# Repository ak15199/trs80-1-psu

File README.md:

# TRS-80 Model 1 Power Supply and Case

A lot of great work has been done by Dan Bear and others over the years to recreate the now virtually impossible to acquire power supply for the TRS-80 Model 1. 

Researching prior art, I set out to create something that - although larger than the original - would not look out of place.

This repository contains the schematic and PCB layout along with the separate models required to 3D print the case. There's also a model to cover the exposed contacts on the fuse caddy.

Once built, you'll need to set the solder jumpers accordingly. There are two links to close if you're running on 110V, and one for 220V. Be careful to ensure that only the correctly labeled jumbers are closed.

Note that I have only built and tested the 110V version, so caution should be taken to test if you're building this to run on 220V.

If you would to use a different case and install an external fuse caddy, then there's a jumper for that too.

The lid of the case is designed to accept four 5.5 dia x 6mm long M4 threaded inserts. I used four M4 x 8mm pan head machine screws to retain the base.

Merge the TRS and Lid STLs if you have a dual extruder system, or don't load the TRS file if you prefer a recessed look. The lid will need to be rotated 180 degrees to avoid supports.

I salvaged the old 2-pin power cable from some old equipment. It was sufficiently thick and inflexible that a cable retainer wasn't needed. If you're not sure, then use a zip tie to bind the cable to the corresponding retaining hole on the PCB.

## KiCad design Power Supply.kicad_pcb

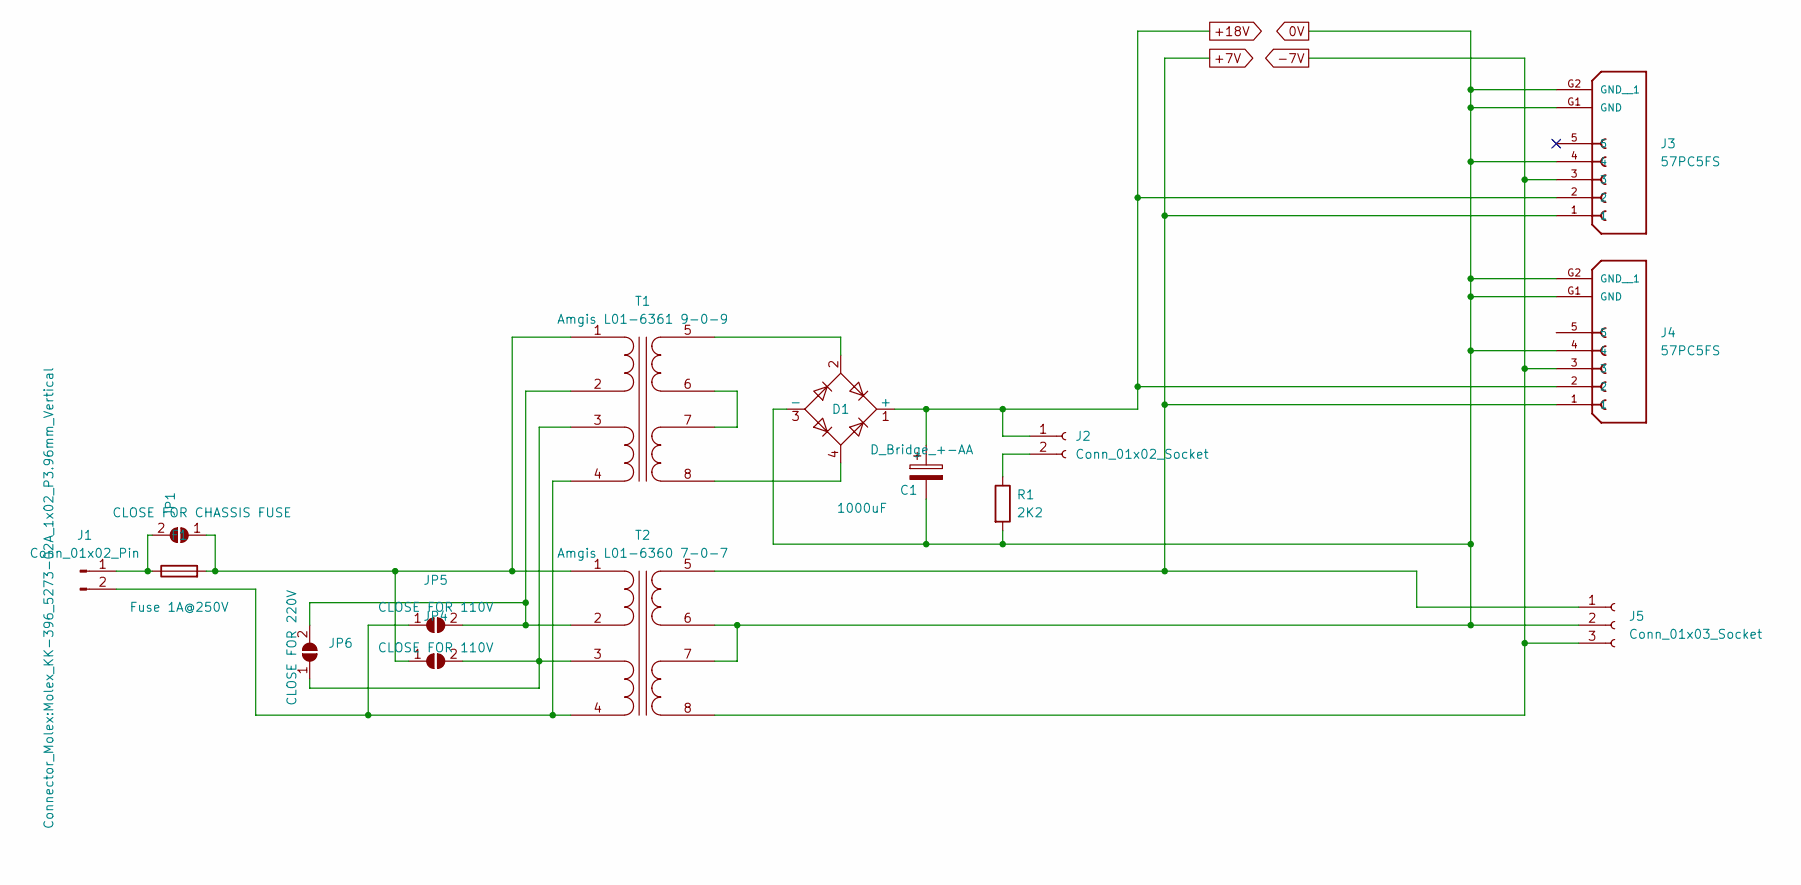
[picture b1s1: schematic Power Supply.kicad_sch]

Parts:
C1: 1000uF; CP_Radial_D13.0mm_P5.00mm
D1: D_Bridge_+-AA; Diode_Bridge_Round_D9.8mm
F1: Fuse 1A@250V; FUSE_0PTF0078P_LTF
J1: Conn_01x02_Pin; Molex_KK-396_5273-02A_1x02_P3.96mm_Vertical
J2: Conn_01x02_Socket; PinHeader_1x02_P2.54mm_Vertical
J3, J4: 57PC5FS; SWITCHCRAFT_57PC5FS; PARTREV C
J5: Conn_01x03_Socket; PinHeader_1x03_P2.54mm_Vertical
JP1: CLOSE FOR CHASSIS FUSE; SolderJumper-2_P1.5mm_Open_RoundedPad1.0x1.5mm
JP4, JP5: CLOSE FOR 110V; SolderJumper-2_P1.5mm_Open_RoundedPad1.0x1.5mm
JP6: CLOSE FOR 220V; SolderJumper-2_P1.5mm_Open_RoundedPad1.0x1.5mm
R1: 2K2; R_Axial_DIN0207_L6.3mm_D2.5mm_P10.16mm_Horizontal
T1: Amgis L01-6361 9-0-9; Amgis 25VA
T2: Amgis L01-6360 7-0-7; Amgis 25VA

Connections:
0V: C1.2, D1.3 (-), J3.4, J3.G1 (GND), J3.G2 (GND__1), J4.4, J4.G1 (GND), J4.G2 (GND__1), J5.2, R1.2, T2.6 (OUT1B), T2.7 (OUT2A)
+7V: J3.1, J4.1, J5.1, T2.5 (OUT1A)
+18V: C1.1, D1.1 (+), J2.1, J3.2, J4.2
-7V: J3.3, J4.3, J5.3, T2.8 (OUT2B)
unnamed: F1.1, J1.1, JP1.2 (B)
unnamed: J1.2, JP5.1 (A), T1.4 (IN2B), T2.4 (IN2B)
unnamed: J2.2, R1.1
unnamed: F1.2, JP1.1 (A), JP4.1 (A), T1.1 (IN1A), T2.1 (IN1A)
unnamed: JP4.2 (B), JP6.1 (A), T1.3 (IN2A), T2.3 (IN2A)
unnamed: JP5.2 (B), JP6.2 (B), T1.2 (IN1B), T2.2 (IN1B)
unnamed: D1.2, T1.5 (OUT1A)
unnamed: T1.6 (OUT1B), T1.7 (OUT2A)
unnamed: D1.4, T1.8 (OUT2B)

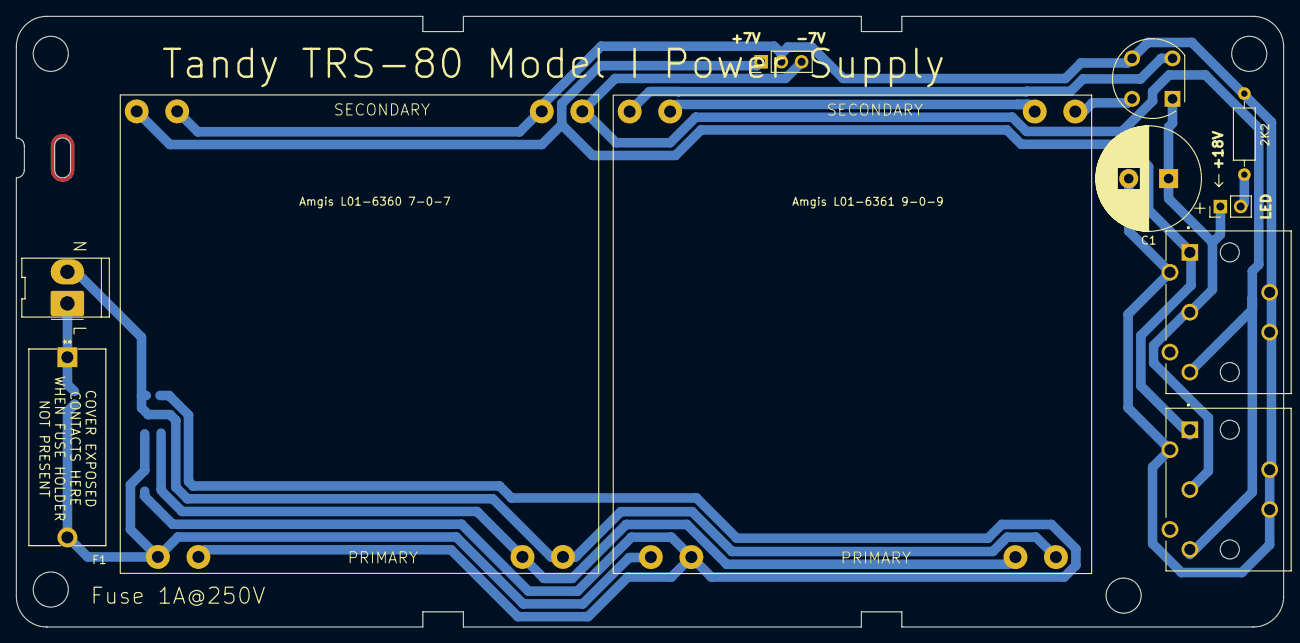
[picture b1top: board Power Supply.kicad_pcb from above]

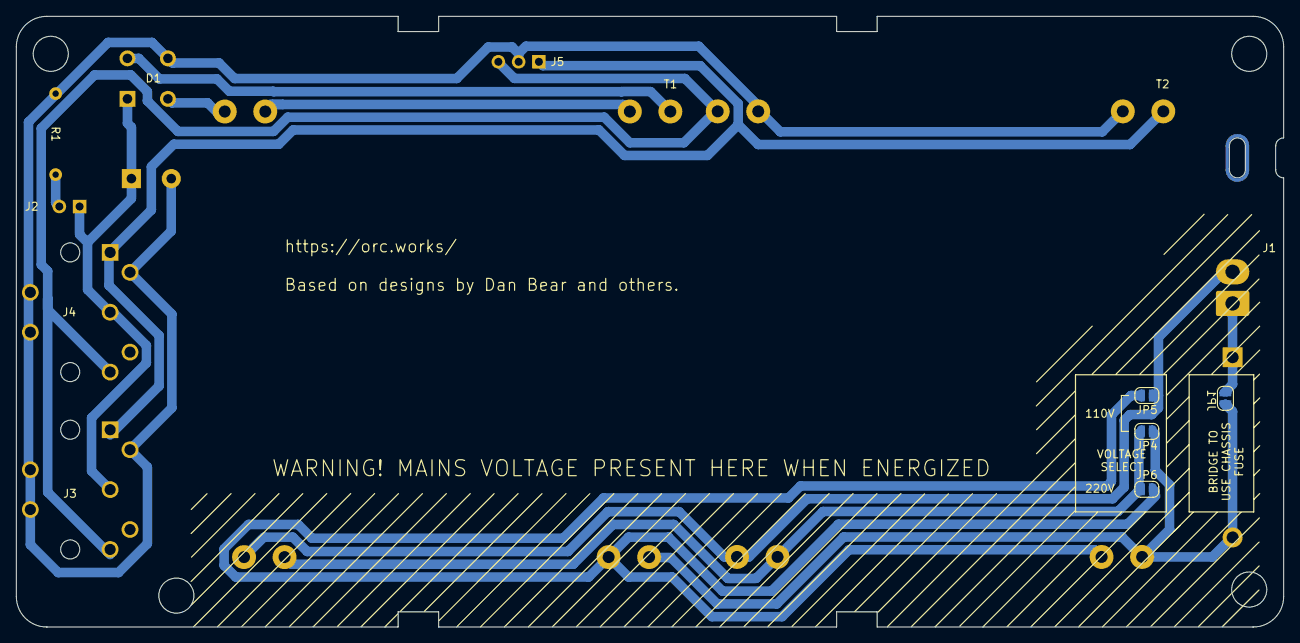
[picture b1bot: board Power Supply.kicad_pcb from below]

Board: 2 copper layers, 158.9 x 76.6 mm, 15 parts (4 on the bottom side), 13 nets.

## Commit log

2024-07-21 Added content
2024-07-21 Added images
2024-07-21 Added README
2024-07-22 Updated README instructions
